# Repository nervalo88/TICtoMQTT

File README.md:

# TICtoMQTT
*interface from french electricity meters to MQTT.*

ENEDIS (former Electricité De France) electricity meter generates some informational signal as Serial ASCII frames e.g:
```
ADCO xxxxxxxxxxxx 2
OPTARIF BASE 0
ISOUSC 30 9
BASE 025298937 8
PTEC TH.. $
IINST 011 Y
IMAX 042 E
PAPP 02550 -
MOTDETAT 000000 B
```
full documentation (french) : https://www.enedis.fr/media/2027/download

## Hardware
Check [./Hardware](./Hardware) for kicad project

## Sofware
### TICtoMQTT
Main software to pass BASE and PPAP values over MQTT
### HWtest
[HWtest](./HWtest) is a quick sketch to get raw frame content

## CAD
Check [./CAD](./CAD) for a 3D printable enclosure for this project, held on DIN rail for electric panels

## References 
[MQTT on ESP](https://randomnerdtutorials.com/esp32-mqtt-publish-subscribe-arduino-ide/)

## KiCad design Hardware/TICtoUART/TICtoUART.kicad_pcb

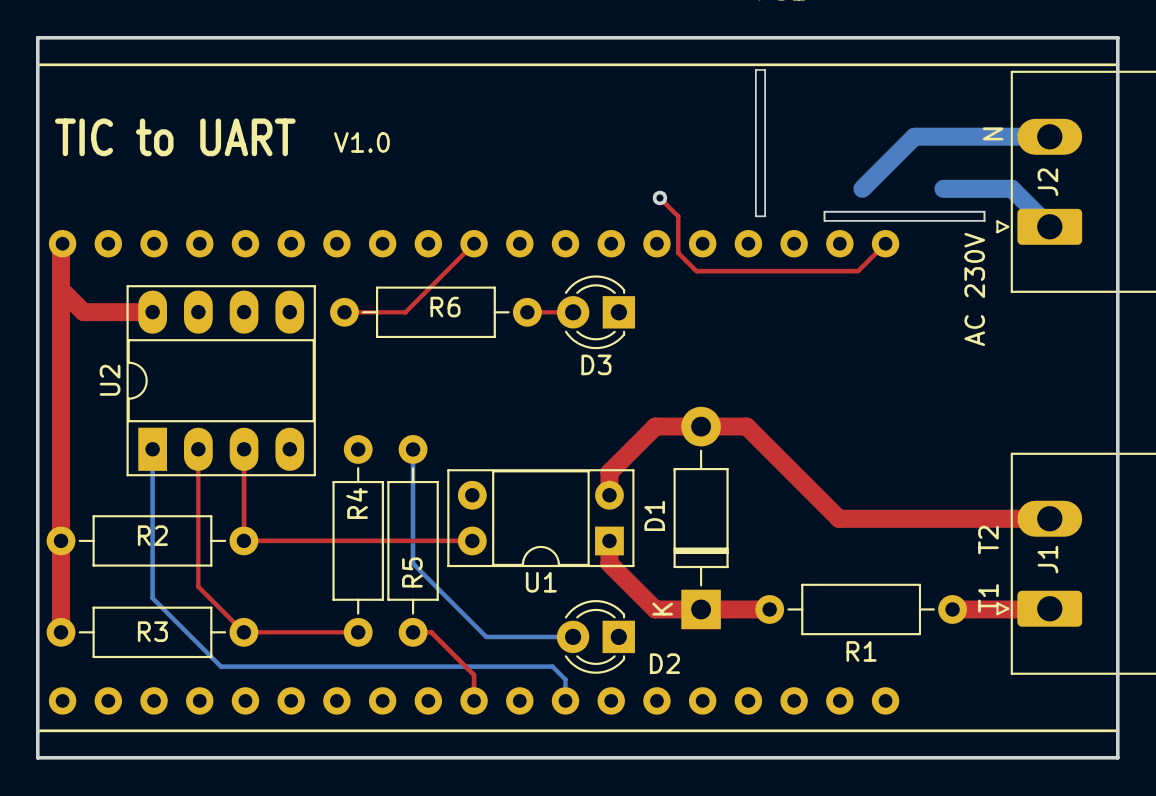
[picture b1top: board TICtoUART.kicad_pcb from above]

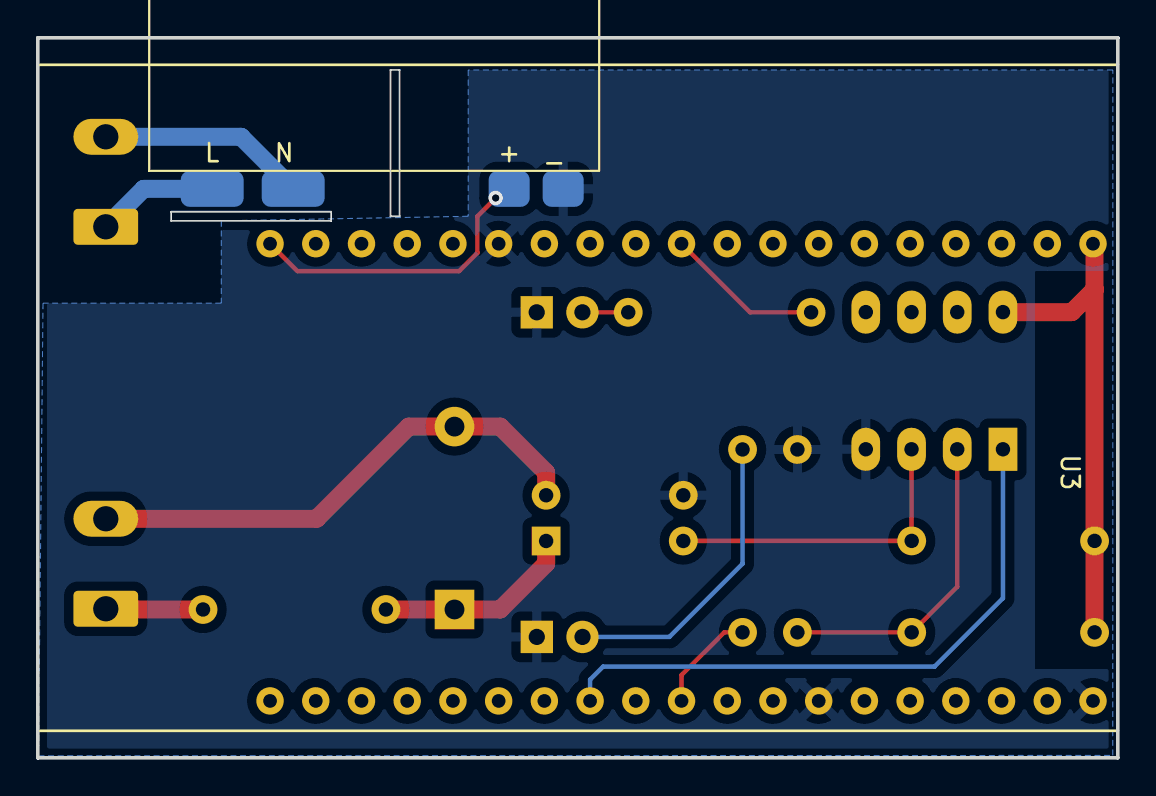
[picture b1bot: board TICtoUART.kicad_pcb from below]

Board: 2 copper layers, 60.0 x 40.0 mm, 15 parts (2 on the bottom side), 15 nets.

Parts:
D1: 1N4001; D_DO-41_SOD81_P10.16mm_Horizontal
D2: Red; LED_D3.0mm
D3: Blue; LED_D3.0mm
J1: Conn_01x02_Male; PhoenixContact_MSTBA_2,5_2-G_1x02_P5.00mm_Horizontal
J2: Conn_01x02_Female; PhoenixContact_MSTBA_2,5_2-G_1x02_P5.00mm_Horizontal
PS1: WX-DC12003
R1: 1k8; R_Axial_DIN0207_L6.3mm_D2.5mm_P10.16mm_Horizontal
R2: R; R_Axial_DIN0207_L6.3mm_D2.5mm_P10.16mm_Horizontal
R3, R4: 120K; R_Axial_DIN0207_L6.3mm_D2.5mm_P10.16mm_Horizontal
R5: 65R; R_Axial_DIN0207_L6.3mm_D2.5mm_P10.16mm_Horizontal
R6: 15R; R_Axial_DIN0207_L6.3mm_D2.5mm_P10.16mm_Horizontal
U1: SFH617A-2X009T; DIP-4_W7.62mm_Socket
U2: LM358; DIP-8_W7.62mm_Socket_LongPads
U3: DOIT-ESP32-DEVKIT-V1; ESP_WROOM_32-DOIT-DEVKIT

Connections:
+3V3: R2.1, R3.1, U2.8 (V+), U3.1 (3V3)
GND: D2.1 (K), D3.1 (K), PS1.3 (-Vout), R4.2, U1.3, U2.4 (V-), U3.14 (GND), U3.32 (GND), U3.38 (GND)
unnamed: D1.1 (K), R1.2, U1.1
unnamed: D1.2 (A), J1.2, U1.2
unnamed: D2.2 (A), R5.2
unnamed: D3.2 (A), R6.2
unnamed: J1.1, R1.1
unnamed: J2.1, PS1.1 (AC(L))
unnamed: J2.2, PS1.2 (AC(N))
unnamed: PS1.4 (+Vout), U3.19 (VIN)
unnamed: R2.2, U1.4, U2.3 (+)
unnamed: R3.2, R4.1, U2.2 (-)
unnamed: U2.1, U3.27 (GPIO16_UART2-RX)
unnamed: R6.1, U3.10 (GPIO26)
unnamed: R5.1, U3.29 (GPIO5_VSPI-CS0)

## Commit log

2022-04-03 Ajoutez les fichiers .gitignore et .gitattributes.
2022-04-03 Ajoutez des fichiers projet.
2022-04-03 1st commit : material test, send raw data to Serial
2022-04-03 parsing to int
2022-04-05 Added wifimanager
2022-04-05 Added Hardware kicad porject
2022-04-10 added MQTT + status LED
2022-04-13 Fully reworked PCB to host an ESP32 devkit Added CAD for enclosuer
